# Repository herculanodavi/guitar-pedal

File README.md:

# guitar-pedal
Electronics project for the course Mixed-Signal Hardware Design with KiCad by Philip Salmony

## System Design
[System Requirements](system_design/requirements.md)

[Part Number Selection](system_design/part_selection.md)

## PCB
[Kicad Schematics](pcb/kicad)

[LTSpice Simulation Files](pcb/simulation)

[Gerber Files](pcb/gerber)

## Firmware
[Firmware Project](firmware)

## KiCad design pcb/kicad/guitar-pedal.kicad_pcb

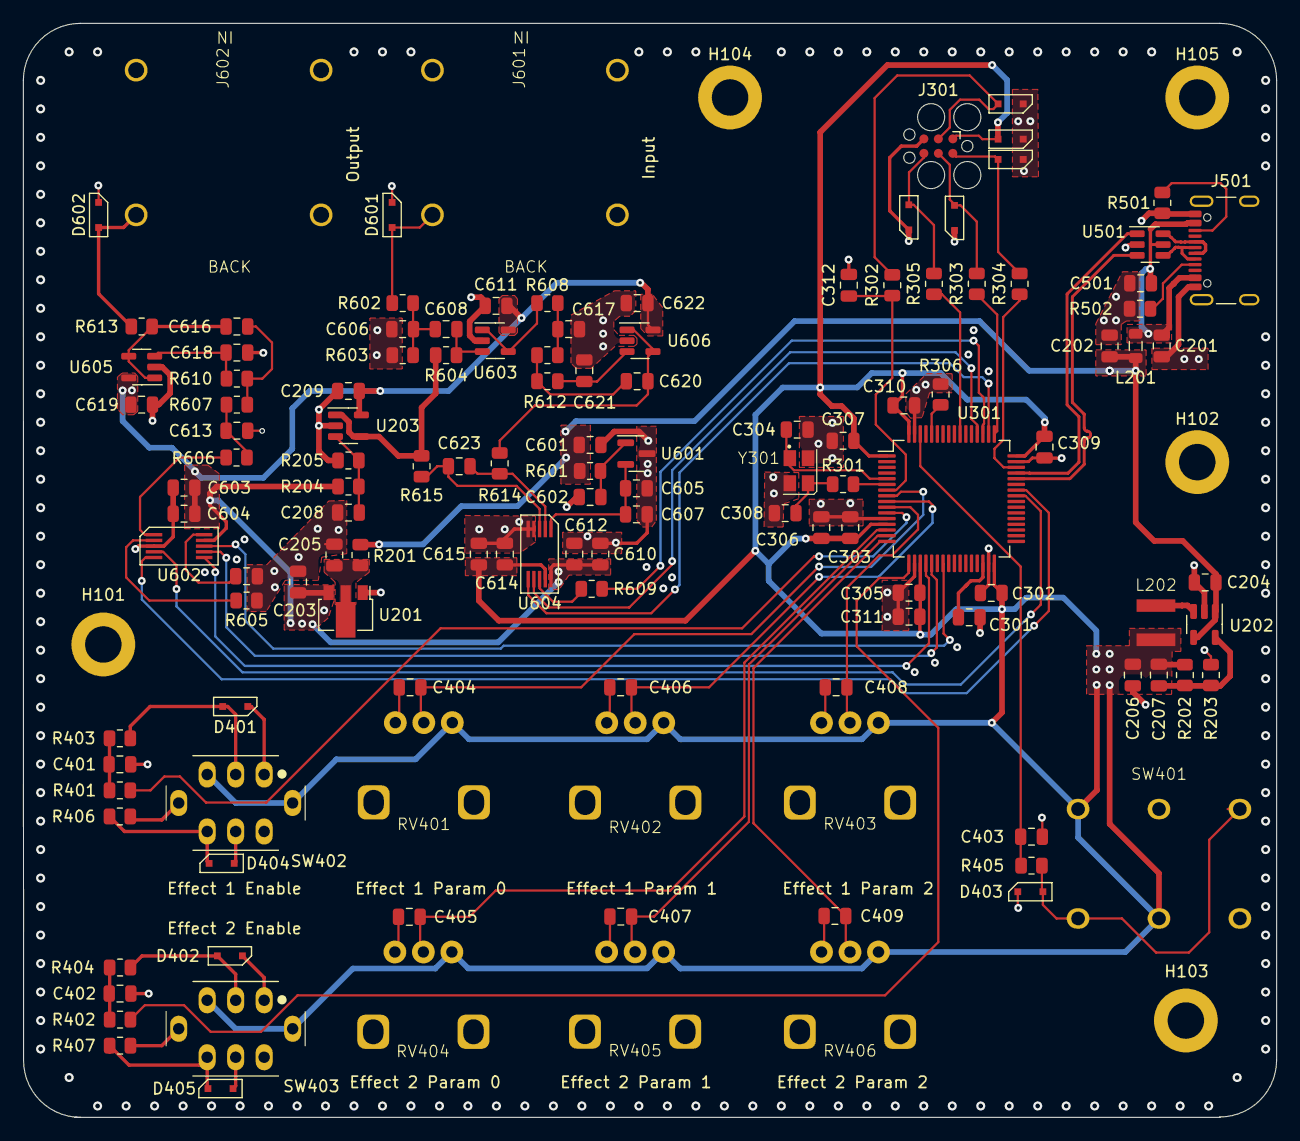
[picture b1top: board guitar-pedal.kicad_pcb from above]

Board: 4 copper layers, 110.0 x 96.0 mm, 133 parts (0 on the bottom side), 76 nets.

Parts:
C201, C202, C306, C609: 1u; C_0805_2012Metric
C203, C204, C205, C206, C208, C501: 22u; C_0805_2012Metric
C207: DNP; C_0805_2012Metric
C209, C302, C303, C305, C307, C309, C310, C312, C401, C402, C403, C404, C405, C406, C407, C408, C409, C604, C607, C608, C611, C612, C614, C619, C622: 100n; C_0805_2012Metric
C301, C311: 4.7u; C_0805_2012Metric
C304, C308: 10p; C_0805_2012Metric
C601, C602, C603, C605, C610, C615: 10u; C_0805_2012Metric
C606, C618, C621, C623: 150p; C_0805_2012Metric
C613, C616, C617, C620: 1n; C_0805_2012Metric
D301, D302, D303, D304, D305, D401, D402, D403, D404, D405, D601, D602: PESD3V3L1BA
H101, H102, H103, H104, H105: MountingHole; MountingHole_3.2mm_M3_DIN965_Pad
J301: TagConnect_TC2030; Tag-Connect_TC2030-IDC-FP_2x03_P1.27mm_Vertical
J501: USB4105-GF-A; USB_C_Receptacle_GCT_USB4105-xx-A_16P_TopMnt_Horizontal
J601, J602: NMJ4HCD2
L201: 10n; L_0805_2012Metric
L202: 68u; ASPI-4030S-680M-T
R201: 10R; R_0805_2012Metric
R202: 100k; R_0805_2012Metric
R203: 22k; R_0805_2012Metric
R204, R205: 1k; R_0805_2012Metric
R301, R609: 0R; R_0805_2012Metric
R302, R303, R304, R305, R601, R613: 49.9R; R_0805_2012Metric
R306, R605: 10K; R_0805_2012Metric
R401, R402, R403, R404, R405, R406, R407, R602, R614, R615: 1K; R_0805_2012Metric
R501, R502: 5K1; R_0805_2012Metric
R603, R604: 2M2; R_0805_2012Metric
R606, R608: 6K8; R_0805_2012Metric
R607, R611: 22K; R_0805_2012Metric
R610, R612: 12K; R_0805_2012Metric
RV401, RV402, RV403, RV404, RV405, RV406: 50K Linear; PTV09A-4030S-A503
SW401: PBS-24-202P; FSW-DPDT-020
SW402, SW403: LP4EE1PBCTR
U201: HT7533-1; SOT-89-3
U202: TLV62569DBV; SOT-23-5
U203, U603, U605, U606: MCP6001-OT; SOT-23-5
U301: STM32F401RBTx; LQFP-64_10x10mm_P0.5mm
U501: USBLC6-2SC6; SOT-23-6
U601: REF3033; SOT-23
U602: DAC7563SDGSR; 10-VSSOP-TI
U604: ADC141S626; 10-VSSOP-TI
Y301: 16MHz; RH100-16.000-8-2020-TR

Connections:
+3.3VA: C205.1, C209.2, C603.1, C604.1, C610.1, C611.2, C612.1, C619.2, C622.2, R204.2, U201.3 (VOUT), U203.5 (V+), U602.9 (AVDD), U603.5 (V+), U604.10 (VA), U605.5 (V+), U606.5 (V+)
+3V3: C206.1, C207.1, C302.1, C303.1, C305.1, C306.1, C307.1, C309.1, C310.1, C311.1, C614.1, C615.1, D301.2 (A2), J301.1 (VCC), L202.2, R202.2, RV401.1, RV402.1, RV403.1, RV404.1, RV405.1, RV406.1, SW401.1 (A), SW401.4 (A), SW402.3, SW402.7 (L1), SW403.3, SW403.7 (L1), U301.1 (VBAT), U301.13 (VREF+), U301.19 (VDD), U301.32 (VDD), U301.48 (VDD), U301.64 (VDD), U604.9 (VIO)
+5V: C202.1, C204.1, C601.1, L201.2, R201.1, R601.1, U202.1 (EN), U202.4 (VIN)
/Data Converters/ADC_IN+: C623.2, R614.2, U604.2 (+IN)
/Data Converters/ADC_IN-: C623.1, R615.2, U604.3 (-IN)
/Data Converters/ADC_MISO: U301.52 (PC11), U604.7 (DOUT)
/Data Converters/ADC_NCS: U301.50 (PA15), U604.6 (nCS)
/Data Converters/ADC_SCLK: R609.2, U301.51 (PC10)
/Data Converters/ADC_VREF: C605.1, C607.1, U601.2 (OUT), U604.1 (VREF)
/Data Converters/ADC_VREF_VIN: C602.1, R601.2, U601.1 (IN)
/Data Converters/DAC_CS: U301.20 (PA4), U602.6 (NSYNC)
/Data Converters/DAC_MOSI: U301.23 (PA7), U602.8 (DIN)
/Data Converters/DAC_NCLR: U301.42 (PA9), U602.5 (NCLR)
/Data Converters/DAC_NLDAC: U301.41 (PA8), U602.4 (NLDAC)
/Data Converters/DAC_SCLK: U301.21 (PA5), U602.7 (SCLK)
/Effect Controls/EFFECT1_EN: R401.1, U301.11 (PC3)
/Effect Controls/EFFECT1_KNOB0: C404.1, RV401.2, U301.8 (PC0)
/Effect Controls/EFFECT1_KNOB1: C406.1, RV402.2, U301.9 (PC1)
/Effect Controls/EFFECT1_KNOB2: C408.1, RV403.2, U301.10 (PC2)
/Effect Controls/EFFECT2_EN: R402.1, U301.17 (PA3)
/Effect Controls/EFFECT2_KNOB0: C405.1, RV404.2, U301.14 (PA0)
/Effect Controls/EFFECT2_KNOB1: C407.1, RV405.2, U301.15 (PA1)
/Effect Controls/EFFECT2_KNOB2: C409.1, RV406.2, U301.16 (PA2)
/Effect Controls/PEDAL_EN: C403.1, R405.1, U301.62 (PB9)
/PowerSupply/5V_FILT: C203.1, R201.2, U201.2 (VIN)
/PowerSupply/BUCK_FB: C207.2, R202.1, R203.2, U202.5 (FB)
/PowerSupply/BUCK_SW: L202.1, U202.3 (SW)
/PowerSupply/VCOM_INPUT: C208.1, R204.1, R205.2, U203.3 (+)
/Processor/BOOT0: R306.2, U301.60 (BOOT0)
/Processor/D+: U301.45 (PA12), U501.1 (I/O1)
/Processor/D-: U301.44 (PA11), U501.3 (I/O2)
/Processor/HSE_IN: C304.1, U301.5 (PH0), Y301.1
/Processor/HSE_OUT: R301.2, U301.6 (PH1)
/Processor/HSE_PRE_OUT: C308.1, R301.1, Y301.3
/Processor/SWCLK: R303.2, U301.49 (PA14)
/Processor/SWDIO: R304.2, U301.46 (PA13)
/Processor/SWO: R305.2, U301.55 (PB3)
/Processor/TAG_SWCLK: D303.2 (A2), J301.4 (SWCLK), R303.1
/Processor/TAG_SWDIO: D304.2 (A2), J301.2 (SWDIO), R304.1
/Processor/TAG_SWO: D305.2 (A2), J301.6 (SWO), R305.1
/Processor/TAG_nRST: D302.2 (A2), J301.3 (~RESET), R302.1
/Processor/VCAP: C301.1, U301.30 (VCAP1)
/Processor/nRST: C312.1, R302.2, U301.7 (NRST)
/USB/CONN_D+: J501.A6 (D+), J501.B6 (D+), U501.6 (I/O1)
/USB/CONN_D-: J501.A7 (D-), J501.B7 (D-), U501.4 (I/O2)
GND: C201.2, C202.2, C203.2, C204.2, C205.2, C206.2, C208.2, C209.1, C301.2, C302.2, C303.2, C304.2, C305.2, C306.2, C307.2, C308.2, C309.2, C310.2, C311.2, C312.2, C401.2, C402.2, C403.2, C404.2, C405.2, C406.2, C407.2, C408.2, C409.2, C501.2, C601.2, C602.2, C603.2, C604.2, C605.2, C606.2, C607.2, C609.1, C610.2, C611.1, C612.2, C613.1, C614.2, C615.2, C617.1, C618.1, C619.1, C621.1, C622.1, D301.1 (A1), D302.1 (A1), D303.1 (A1), D304.1 (A1), D305.1 (A1), D401.1 (A1), D402.1 (A1), D403.1 (A1), D404.2 (A2), D405.2 (A2), D601.1 (A1), D602.1 (A1), J301.5 (GND), J501.A1 (GND), J501.A12 (GND), J501.B1 (GND), J501.B12 (GND), J601.2, J601.3, J601.4, J602.2, J602.3, J602.4, R203.1, R205.1, R306.1, R501.1, R502.1, R603.2, R605.1, RV401.3, RV402.3, RV403.3, RV404.3, RV405.3, RV406.3, SW401.3 (C), SW401.6 (C), SW402.1, SW402.5, SW403.1, SW403.5, U201.1 (GND), U202.2 (GND), U203.2 (V-), U301.12 (VSSA), U301.18 (VSS), U301.31 (VSS), U301.47 (VSS), U301.63 (VSS), U501.2 (GND), U601.3 (GND), U602.3 (GND), U603.2 (V-), U604.4 (GND), U604.5 (GND), U605.2 (V-), U606.2 (V-), Y301.2, Y301.4
unnamed: C401.1, R401.2, R403.1
unnamed: C402.1, R402.2, R404.1
unnamed: C606.1, C608.1, R602.2, R603.1
unnamed: C613.2, R606.2, R607.1
unnamed: C616.2, R607.2, R610.1
unnamed: C617.2, R608.2, R611.1
unnamed: C620.2, R611.2, R612.1
unnamed: D401.2 (A2), R403.2, SW402.2
unnamed: D402.2 (A2), R404.2, SW403.2
unnamed: D403.2 (A2), R405.2, SW401.2 (B), SW401.5 (B)
unnamed: D404.1 (A1), R406.2, SW402.6
unnamed: D405.1 (A1), R407.2, SW403.6
unnamed: D601.2 (A2), J601.1, R602.1
unnamed: D602.2 (A2), J602.1, R613.2
unnamed: J501.A5 (CC1), R502.2
unnamed: J501.B5 (CC2), R501.2
unnamed: R406.1, SW402.8 (L2)
unnamed: R407.1, SW403.8 (L2)
unnamed: R606.1, U602.1 (VOUT_A)
unnamed: R605.2, U602.2 (VOUT_B)
unnamed: C609.2, U602.10 (VREFIN/OUT)
unnamed: C608.2, R604.2, U603.3 (+)
unnamed: R608.1, U603.1, U603.4 (-)
unnamed: R609.1, U604.8 (SCLK)
unnamed: C618.2, R610.2, U605.3 (+)
unnamed: C616.1, R613.1, U605.1, U605.4 (-)
unnamed: C621.2, R612.2, U606.3 (+)
unnamed: C620.1, R614.1, U606.1, U606.4 (-)
VBUS: C201.1, C501.1, J501.A4 (VBUS), J501.A9 (VBUS), J501.B4 (VBUS), J501.B9 (VBUS), L201.1, U501.5 (VBUS)
VCOM: R604.1, R615.1, U203.1, U203.4 (-)

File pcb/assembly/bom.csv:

"Source:","/Users/apre/davi/guitar-pedal/pcb/kicad/guitar-pedal.kicad_sch"
"Date:","2023 December 28, Thursday 00:46:10"
"Tool:","Eeschema 7.0.8"
"Generator:","/Applications/KiCad/KiCad.app/Contents/SharedSupport/plugins/bom_csv_grouped_by_value_with_fp.py"
"Component Count:","132"
"Ref","Qnty","Value","Cmp name","Footprint","Description","Vendor","DNP"
"C201, C202, C306, C609","4","1u","C","Capacitor_SMD:C_0805_2012Metric","Unpolarized capacitor","",""
"C203, C204, C205, C206, C208, C501","6","22u","C","Capacitor_SMD:C_0805_2012Metric","Unpolarized capacitor","",""
"C207","1","DNP","C","Capacitor_SMD:C_0805_2012Metric","Unpolarized capacitor","",""
"C209, C302, C303, C305, C307, C309, C310, C312, C401, C402, C403, C404, C405, C406, C407, C408, C409, C604, C607, C611, C612, C614, C619, C622","24","100n","C","Capacitor_SMD:C_0805_2012Metric","Unpolarized capacitor","",""
"C301, C311","2","4.7u","C","Capacitor_SMD:C_0805_2012Metric","Unpolarized capacitor","",""
"C304, C308","2","10p","C","Capacitor_SMD:C_0805_2012Metric","Unpolarized capacitor","",""
"C601, C602, C603, C605, C610, C615","6","10u","C","Capacitor_SMD:C_0805_2012Metric","Unpolarized capacitor","",""
"C606, C608, C618, C621, C623","5","150p","C","Capacitor_SMD:C_0805_2012Metric","Unpolarized capacitor","",""
"C613, C616, C617, C620","4","1n","C","Capacitor_SMD:C_0805_2012Metric","Unpolarized capacitor","",""
"D301, D302, D303, D304, D305, D401, D402, D403, D404, D405, D601, D602","12","~","PESD3V3L1BA","pedal-components:PESD3V3L1BA","","",""
"H101, H102, H103, H104, H105","5","MountingHole","MountingHole","MountingHole:MountingHole_3.2mm_M3_DIN965_Pad","Mounting Hole without connection","",""
"J501","1","USB4105-GF-A","USB_C_Receptacle_USB2.0","Connector_USB:USB_C_Receptacle_GCT_USB4105-xx-A_16P_TopMnt_Horizontal","USB 2.0-only Type-C Receptacle connector","",""
"J601, J602","2","NMJ4HCD2","NMJ4HCD2","pedal-components:NMJ4HCD2","","",""
"L201","1","10n","L","Inductor_SMD:L_0805_2012Metric","Inductor","",""
"L202","1","68u","L","pedal-components:ASPI-4030S-680M-T","Inductor","",""
"R201","1","10R","R","Resistor_SMD:R_0805_2012Metric","Resistor","",""
"R202","1","100k","R","Resistor_SMD:R_0805_2012Metric","Resistor","",""
"R203","1","22k","R","Resistor_SMD:R_0805_2012Metric","Resistor","",""
"R204, R205","2","1k","R","Resistor_SMD:R_0805_2012Metric","Resistor","",""
"R301, R609","2","0R","R","Resistor_SMD:R_0805_2012Metric","Resistor","",""
"R302, R303, R304, R305, R601, R613","6","49.9R","R","Resistor_SMD:R_0805_2012Metric","Resistor","",""
"R306, R605","2","10K","R","Resistor_SMD:R_0805_2012Metric","Resistor","",""
"R401, R402, R403, R404, R405, R406, R407, R602, R614, R615","10","1K","R","Resistor_SMD:R_0805_2012Metric","Resistor","",""
"R501, R502","2","5K1","R","Resistor_SMD:R_0805_2012Metric","Resistor","",""
"R603, R604","2","2M2","R","Resistor_SMD:R_0805_2012Metric","Resistor","",""
"R606, R608","2","6K8","R","Resistor_SMD:R_0805_2012Metric","Resistor","",""
"R607, R611","2","22K","R","Resistor_SMD:R_0805_2012Metric","Resistor","",""
"R610, R612","2","12K","R","Resistor_SMD:R_0805_2012Metric","Resistor","",""
"RV401, RV402, RV403, RV404, RV405, RV406","6","50K Linear","R_Potentiometer","pedal-components:PTV09A-4030S-A503","Potentiometer","",""
"SW401","1","PBS-24-202P","SW_Push_DPDT","pedal-components:FSW-DPDT-020","Momentary Switch, dual pole double throw","",""
"SW402, SW403","2","LP4EE1PBCTR","LP4EE1PBCTR","pedal-components:LP4EE1PBCTR","","",""
"U201","1","HT7533-1","HT75xx-1-SOT89_1","Package_TO_SOT_SMD:SOT-89-3","100mA Low Dropout Voltage Regulator, Fixed Output, SOT89","",""
"U202","1","TLV62569DBV","TLV62569DBV","Package_TO_SOT_SMD:SOT-23-5","High Efficiency Synchronous Buck Converter, Adjustable Output 0.6V-5.5V, 2A, SOT-23-5","",""
"U203, U603, U605, U606","4","MCP6001-OT","MCP6001-OT","Package_TO_SOT_SMD:SOT-23-5","1MHz, Low-Power Op Amp, SOT-23-5","",""
"U301","1","STM32F401RBTx","STM32F401RBTx","Package_QFP:LQFP-64_10x10mm_P0.5mm","STMicroelectronics Arm Cortex-M4 MCU, 128KB flash, 64KB RAM, 84 MHz, 1.7-3.6V, 50 GPIO, LQFP64","",""
"U501","1","USBLC6-2SC6","USBLC6-2SC6","Package_TO_SOT_SMD:SOT-23-6","Very low capacitance ESD protection diode, 2 data-line, SOT-23-6","",""
"U601","1","REF3033","REF3033","Package_TO_SOT_SMD:SOT-23","3.3V 50-ppm/°C Max, 50-μA, CMOS Voltage Reference, SOT-23-3","",""
"U602","1","DAC7563SDGSR","DAC7563SDGSR","pedal-components:10-VSSOP-TI","","",""
"U604","1","ADC141S626","ADC141S626","pedal-components:10-VSSOP-TI","","",""
"Y301","1","16MHz","Crystal_GND24","pedal-components:RH100-16.000-8-2020-TR","Four pin crystal, GND on pins 2 and 4","",""

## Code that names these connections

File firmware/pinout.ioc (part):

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Mcu.Name=STM32F401R(B-C)Tx
Mcu.Package=LQFP64
Mcu.UserName=STM32F401RBTx
PA0-WKUP.GPIOParameters=GPIO_Label
PA0-WKUP.GPIO_Label=EFFECT2_KNOB0
PA0-WKUP.Signal=ADCx_IN0
PA1.GPIOParameters=GPIO_Label
PA1.GPIO_Label=EFFECT2_KNOB1
PA1.Signal=ADCx_IN1
PA11.GPIOParameters=GPIO_Label
PA11.GPIO_Label=USB_N
PA11.Mode=Device_Only
PA11.Signal=USB_OTG_FS_DM
PA12.GPIOParameters=GPIO_Label
PA12.GPIO_Label=USB_P
PA12.Mode=Device_Only
PA12.Signal=USB_OTG_FS_DP
PA13.GPIOParameters=GPIO_Label
PA13.GPIO_Label=PROG_SWDIO
PA13.Mode=Trace_Asynchronous_SW
PA13.Signal=SYS_JTMS-SWDIO
PA14.GPIOParameters=GPIO_Label
PA14.GPIO_Label=PROG_SWCLK
PA14.Mode=Trace_Asynchronous_SW
PA14.Signal=SYS_JTCK-SWCLK
PA15.GPIOParameters=GPIO_Label
PA15.GPIO_Label=ADC_NCS
PA15.Mode=NSS_Signal_Hard_Output
PA15.Signal=SPI3_NSS
PA2.GPIOParameters=GPIO_Label
PA2.GPIO_Label=EFFECT2_KNOB2
PA2.Signal=ADCx_IN2
PA3.GPIOParameters=GPIO_Label
PA3.GPIO_Label=EFFECT2_EN
PA3.Signal=GPIO_Input
PA4.GPIOParameters=GPIO_Label
PA4.GPIO_Label=DAC_NCS
PA4.Mode=NSS_Signal_Hard_Output
PA4.Signal=SPI1_NSS
PA5.GPIOParameters=GPIO_Label
PA5.GPIO_Label=DAC_SCLK
PA5.Mode=TX_Only_Simplex_Unidirect_Master
PA5.Signal=SPI1_SCK
PA7.GPIOParameters=GPIO_Label
PA7.GPIO_Label=DAC_MOSI
PA7.Mode=TX_Only_Simplex_Unidirect_Master
PA7.Signal=SPI1_MOSI
PA8.GPIOParameters=GPIO_Label
PA8.GPIO_Label=DAC_NLDAC
PA8.Signal=GPIO_Output
PA9.GPIOParameters=GPIO_Label
PA9.GPIO_Label=DAC_NCLR
PA9.Signal=GPIO_Output
PB0.GPIOParameters=GPIO_Label
PB0.GPIO_Label=DAC_INT
PB0.Signal=GPXTI0
PB3.GPIOParameters=GPIO_Label
PB3.GPIO_Label=PROG_SWO
PB3.Mode=Trace_Asynchronous_SW
PB3.Signal=SYS_JTDO-SWO
PB9.GPIOParameters=GPIO_Label
PB9.GPIO_Label=PEDAL_EN
PB9.Signal=GPIO_Input
PC0.GPIOParameters=GPIO_Label
PC0.GPIO_Label=EFFECT1_KNOB0
PC0.Signal=ADCx_IN10
PC1.GPIOParameters=GPIO_Label
PC1.GPIO_Label=EFFECT1_KNOB1
PC1.Signal=ADCx_IN11
PC10.GPIOParameters=GPIO_Label
PC10.GPIO_Label=ADC_SCLK
PC10.Mode=RX_Only_Simplex_Unidirect_Master
PC10.Signal=SPI3_SCK
PC11.GPIOParameters=GPIO_Label
PC11.GPIO_Label=ADC_MISO
PC11.Mode=RX_Only_Simplex_Unidirect_Master
PC11.Signal=SPI3_MISO
PC2.GPIOParameters=GPIO_Label
PC2.GPIO_Label=EFFECT1_KNOB2
PC2.Signal=ADCx_IN12
PC3.GPIOParameters=GPIO_Label
PC3.GPIO_Label=EFFECT1_EN
PC3.Signal=GPIO_Input
PH0\ -\ OSC_IN.GPIOParameters=GPIO_Label
PH0\ -\ OSC_IN.GPIO_Label=HSE_IN
PH0\ -\ OSC_IN.Mode=HSE-External-Oscillator
PH0\ -\ OSC_IN.Signal=RCC_OSC_IN
PH1\ -\ OSC_OUT.GPIOParameters=GPIO_Label
PH1\ -\ OSC_OUT.GPIO_Label=HSE_OUT
PH1\ -\ OSC_OUT.Mode=HSE-External-Oscillator
PH1\ -\ OSC_OUT.Signal=RCC_OSC_OUT
RCC.HSE_VALUE=25000000
RCC.SYSCLKFreq_VALUE=16000000
board=custom

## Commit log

2023-11-26 Add system requirements
2023-11-26 Add luminance to LED requirement
2023-11-26 Add part selection for MCU, regulator and converters
2023-11-26 Add intro and start effect controls part selection
2023-11-27 Add USB parts
2023-11-29 Add knob and LED in parts selection.
2023-12-10 Add top-level schematic sheet.
2023-12-10 Add power supply circuit and MCU symbol.
2023-12-10 Move project files to kicad directory.
2023-12-10 Add bias generator.
2023-12-10 Move USB to own sheet.
2023-12-10 Add SoC and pinout.
2023-12-10 Add CubeMX configuration file.
2023-12-17 Fix detailed block diagram.
2023-12-17 Add hse circuit.
2023-12-17 Added ADC digital part.
2023-12-26 Added converters, controls and updated annotations.
2023-12-26 Started PCB placement.
2023-12-28 Added PCB layout and fabrication output.
2023-12-29 Add ltspice simulations.
2023-12-29 Update README.md links
2023-12-29 Fix newlines in README.md
2023-12-29 Update .ioc file and fix DAC pinout.
2023-12-29 Add part numbers to components for ordering.
